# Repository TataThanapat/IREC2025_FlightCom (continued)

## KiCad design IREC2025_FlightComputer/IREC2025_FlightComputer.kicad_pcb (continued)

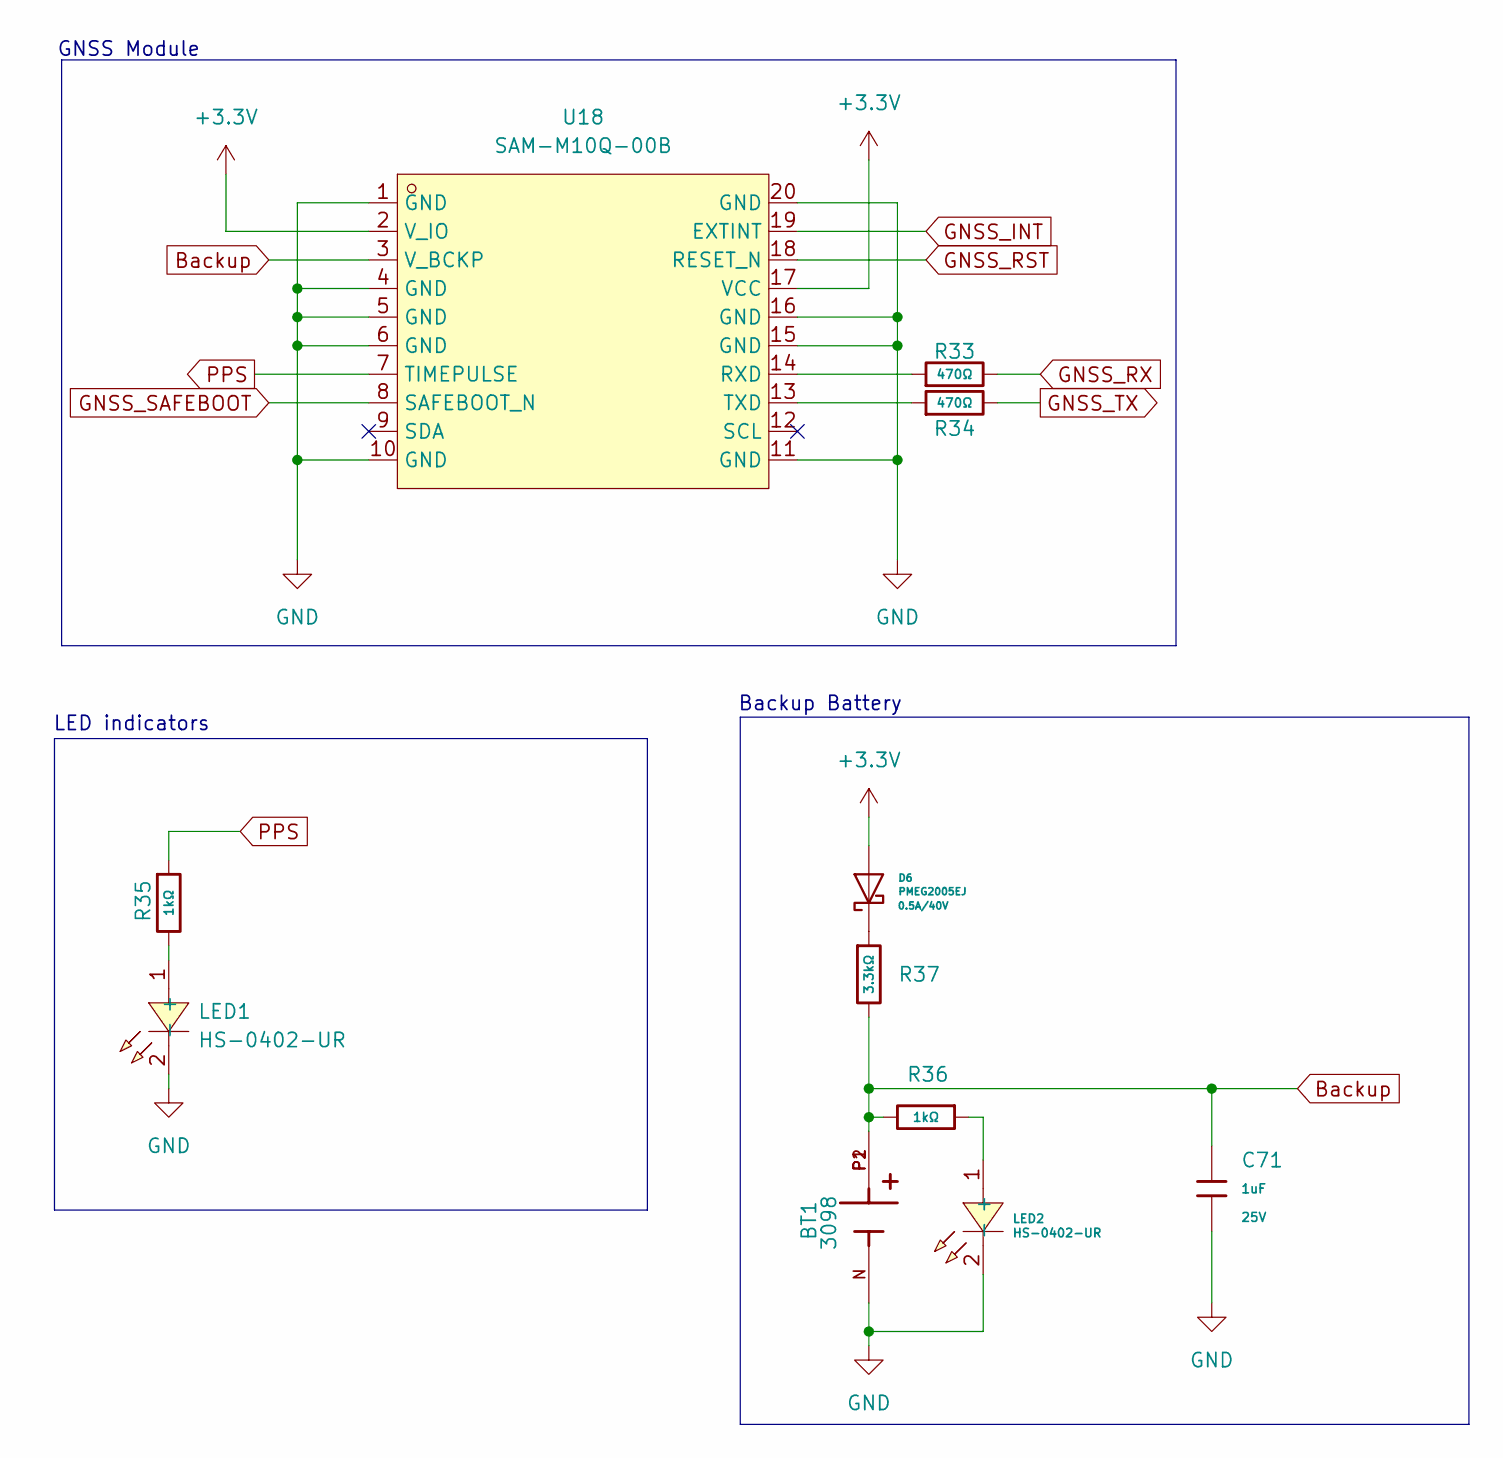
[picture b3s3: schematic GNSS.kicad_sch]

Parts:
BT1: 3098; BAT_3098; PARTREV K
C71: 1uF; C_0402; Voltage Rated 25V; Tolerance ±10%; Part CL05A105KA5NQNC; LCSC C52923
D6: PMEG2005EJ; D_SOD-323F; Ratings 0.5A/40V
LED1, LED2: HS-0402-UR; LED0402-R-RD; LCSC Part C1322304
R33, R34: 470Ω; R_0402; Overload Voltage (Max) 50V; Tolerance ±1%; Part 0402WGF4700TCE; LCSC C25117
R35, R36: 1kΩ; R_0402; Overload Voltage (Max) 50V; Tolerance ±1%; Part 0402WGF1001TCE; LCSC C11702
R37: 3.3kΩ; R_0402; Overload Voltage (Max) 50V; Tolerance ±1%; Part 0402WGF3301TCE; LCSC C25890
U18: SAM-M10Q-00B; LCC-20_L15.5-W15.5-P1.90_SAM-M10Q-00B; LCSC Part C5443880

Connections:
+3.3V: D6.2 (A), U18.2 (V_IO), U18.17 (VCC); also elsewhere on the board
Backup: BT1.P1, BT1.P2, C71.1, R36.2, R37.2, U18.3 (V_BCKP)
GNSS_INT: U18.19 (EXTINT); also elsewhere on the board
GNSS_RST: U18.18 (RESET_N); also elsewhere on the board
GNSS_RX: R33.2; also elsewhere on the board
GNSS_SAFEBOOT: U18.8 (SAFEBOOT_N); also elsewhere on the board
GNSS_TX: R34.2; also elsewhere on the board
unnamed: D6.1 (K), R37.1
unnamed: LED1.1 (+), R35.2
unnamed: LED2.1 (+), R36.1
unnamed: R33.1, U18.14 (RXD)
unnamed: R34.1, U18.13 (TXD)
PPS: R35.1, U18.7 (TIMEPULSE)
VBAT-: BT1.N, C71.2, LED1.2 (-), LED2.2 (-), U18.1 (GND), U18.4 (GND), U18.5 (GND), U18.6 (GND), U18.10 (GND), U18.11 (GND), U18.15 (GND), U18.16 (GND), U18.20 (GND); also elsewhere on the board

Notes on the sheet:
GNSS Module
LED indicators
Backup Battery

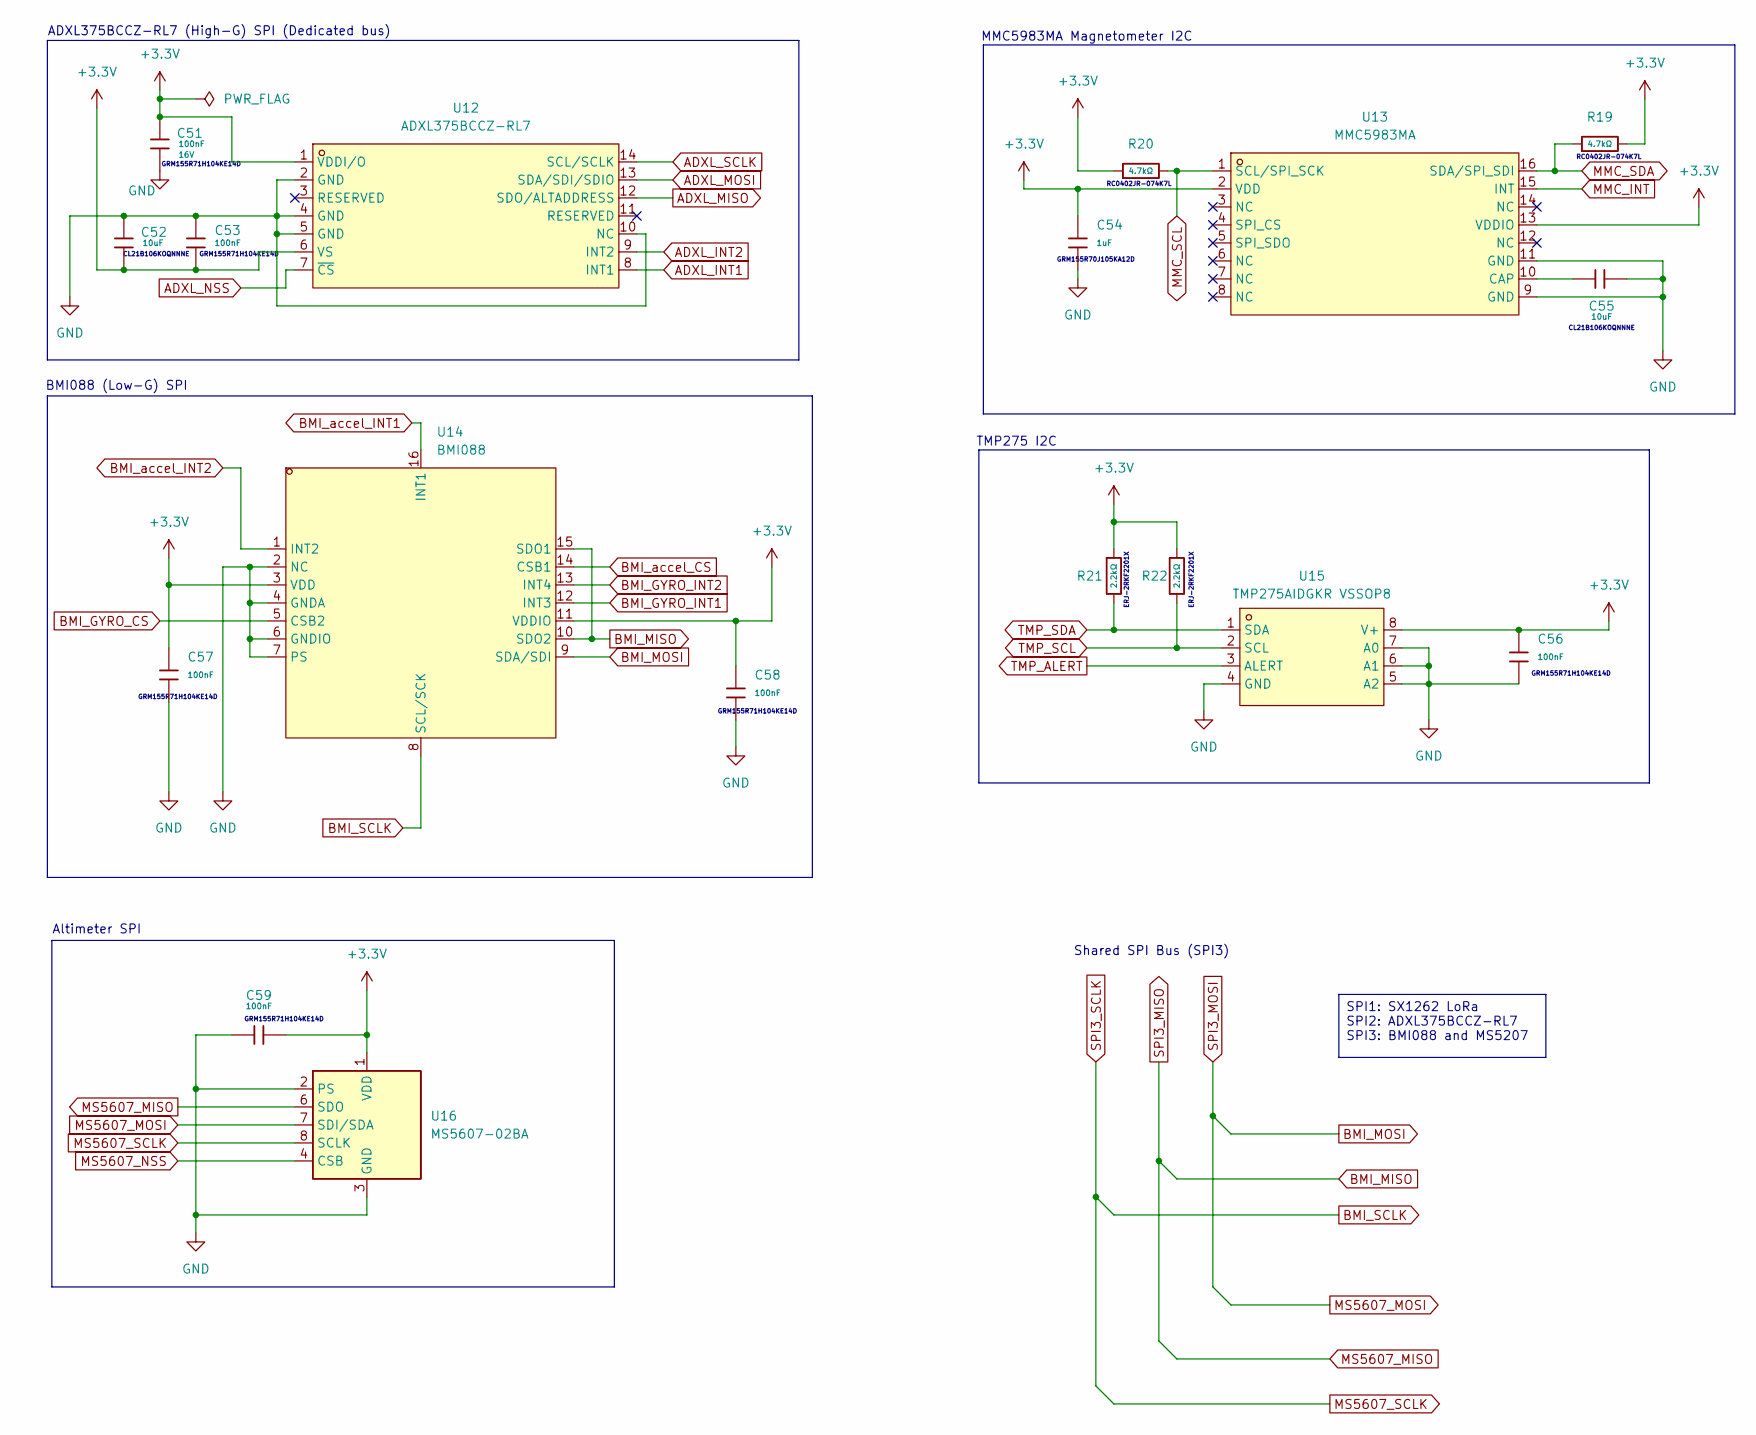
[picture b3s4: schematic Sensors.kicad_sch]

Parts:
C51, C53, C56, C57, C58, C59: 100nF; C_0402; Voltage Rated 16V; Tolerance ±10%; Part CL05B104KO5NNNC; LCSC C1525
C52, C55: 10uF; C_0402; Voltage Rated 6.3V; Tolerance ±20%; Part CL05A106MQ5NUNC; LCSC C15525
C54: 1uF; C_0402; Voltage Rated 25V; Tolerance ±10%; Part CL05A105KA5NQNC; LCSC C52923
R19, R20: 4.7kΩ; R_0402; Overload Voltage (Max) 50V; Tolerance ±1%; Part 0402WGF4701TCE; LCSC C25900
R21, R22: 2.2kΩ; R_0402; Overload Voltage (Max) 50V; Tolerance ±1%; Part 0402WGF2201TCE; LCSC C25879
U12: ADXL375BCCZ-RL7; LGA-14_L5.0-W3.0-P0.80-BL; LCSC Part C481898
U13: MMC5983MA; LGA-16_L3.0-W3.0-P0.50-BL_SQ; LCSC Part C404329
U14: BMI088; LGA-16_L4.5-W3.0-P0.50-BL; LCSC Part C194919
U15: TMP275AIDGKR VSSOP8; VSSOP-8_L3.0-W3.0-P0.65-LS5.0-BL; LCSC Part C87815
U16: MS5607-02BA; LGA-8_3x5mm_P1.25mm

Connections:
+3.3V: C51.1, C52.2, C53.2, C54.1, C56.1, C57.1, C58.1, C59.2, R19.2, R20.1, R21.1, R22.1, U12.1 (VDDI/O), U12.6 (VS), U13.2 (VDD), U13.13 (VDDIO), U14.3 (VDD), U14.11 (VDDIO), U15.8 (V+), U16.1 (VDD); also elsewhere on the board
ADXL_INT1: U12.8 (INT1); also elsewhere on the board
ADXL_INT2: U12.9 (INT2); also elsewhere on the board
ADXL_MISO: U12.12 (SDO/ALTADDRESS); also elsewhere on the board
ADXL_MOSI: U12.13 (SDA/SDI/SDIO); also elsewhere on the board
ADXL_NSS: U12.7 (~CS); also elsewhere on the board
ADXL_SCLK: U12.14 (SCL/SCLK); also elsewhere on the board
BMI_GYRO_CS: U14.5 (CSB2); also elsewhere on the board
BMI_GYRO_INT1: U14.12 (INT3); also elsewhere on the board
BMI_GYRO_INT2: U14.13 (INT4); also elsewhere on the board
BMI_accel_CS: U14.14 (CSB1); also elsewhere on the board
BMI_accel_INT1: U14.16 (INT1); also elsewhere on the board
BMI_accel_INT2: U14.1 (INT2); also elsewhere on the board
MMC_INT: U13.15 (INT); also elsewhere on the board
MMC_SCL: R20.2, U13.1 (SCL/SPI_SCK); also elsewhere on the board
MMC_SDA: R19.1, U13.16 (SDA/SPI_SDI); also elsewhere on the board
MS5607_NSS: U16.4 (CSB), U16.5 (CSB); also elsewhere on the board
unnamed: C55.1, U13.10 (CAP)
TMP_ALERT: U15.3 (ALERT); also elsewhere on the board
TMP_SCL: R22.2, U15.2 (SCL); also elsewhere on the board
TMP_SDA: R21.2, U15.1 (SDA); also elsewhere on the board
VBAT-: C51.2, C52.1, C53.1, C54.2, C55.2, C56.2, C57.2, C58.2, C59.1, U12.2 (GND), U12.4 (GND), U12.5 (GND), U12.10 (NC), U13.9 (GND), U13.11 (GND), U14.2 (NC), U14.4 (GNDA), U14.6 (GNDIO), U14.7 (PS), U15.4 (GND), U15.5 (A2), U15.6 (A1), U15.7 (A0), U16.2 (PS), U16.3 (GND); also elsewhere on the board

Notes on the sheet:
Shared SPI Bus (SPI3)
ERJ-2RKF2201X
CL21B106KOQNNNE
GRM155R71H104KE14D
RC0402JR-074K7L
GRM155R70J105KA12D
TMP275 I2C
BMI088 (Low-G) SPI
MMC5983MA Magnetometer I2C
ADXL375BCCZ-RL7 (High-G) SPI (Dedicated bus)
Altimeter SPI
SPI1: SX1262 LoRa SPI2: ADXL375BCCZ-RL7 SPI3: BMI088 and MS5207

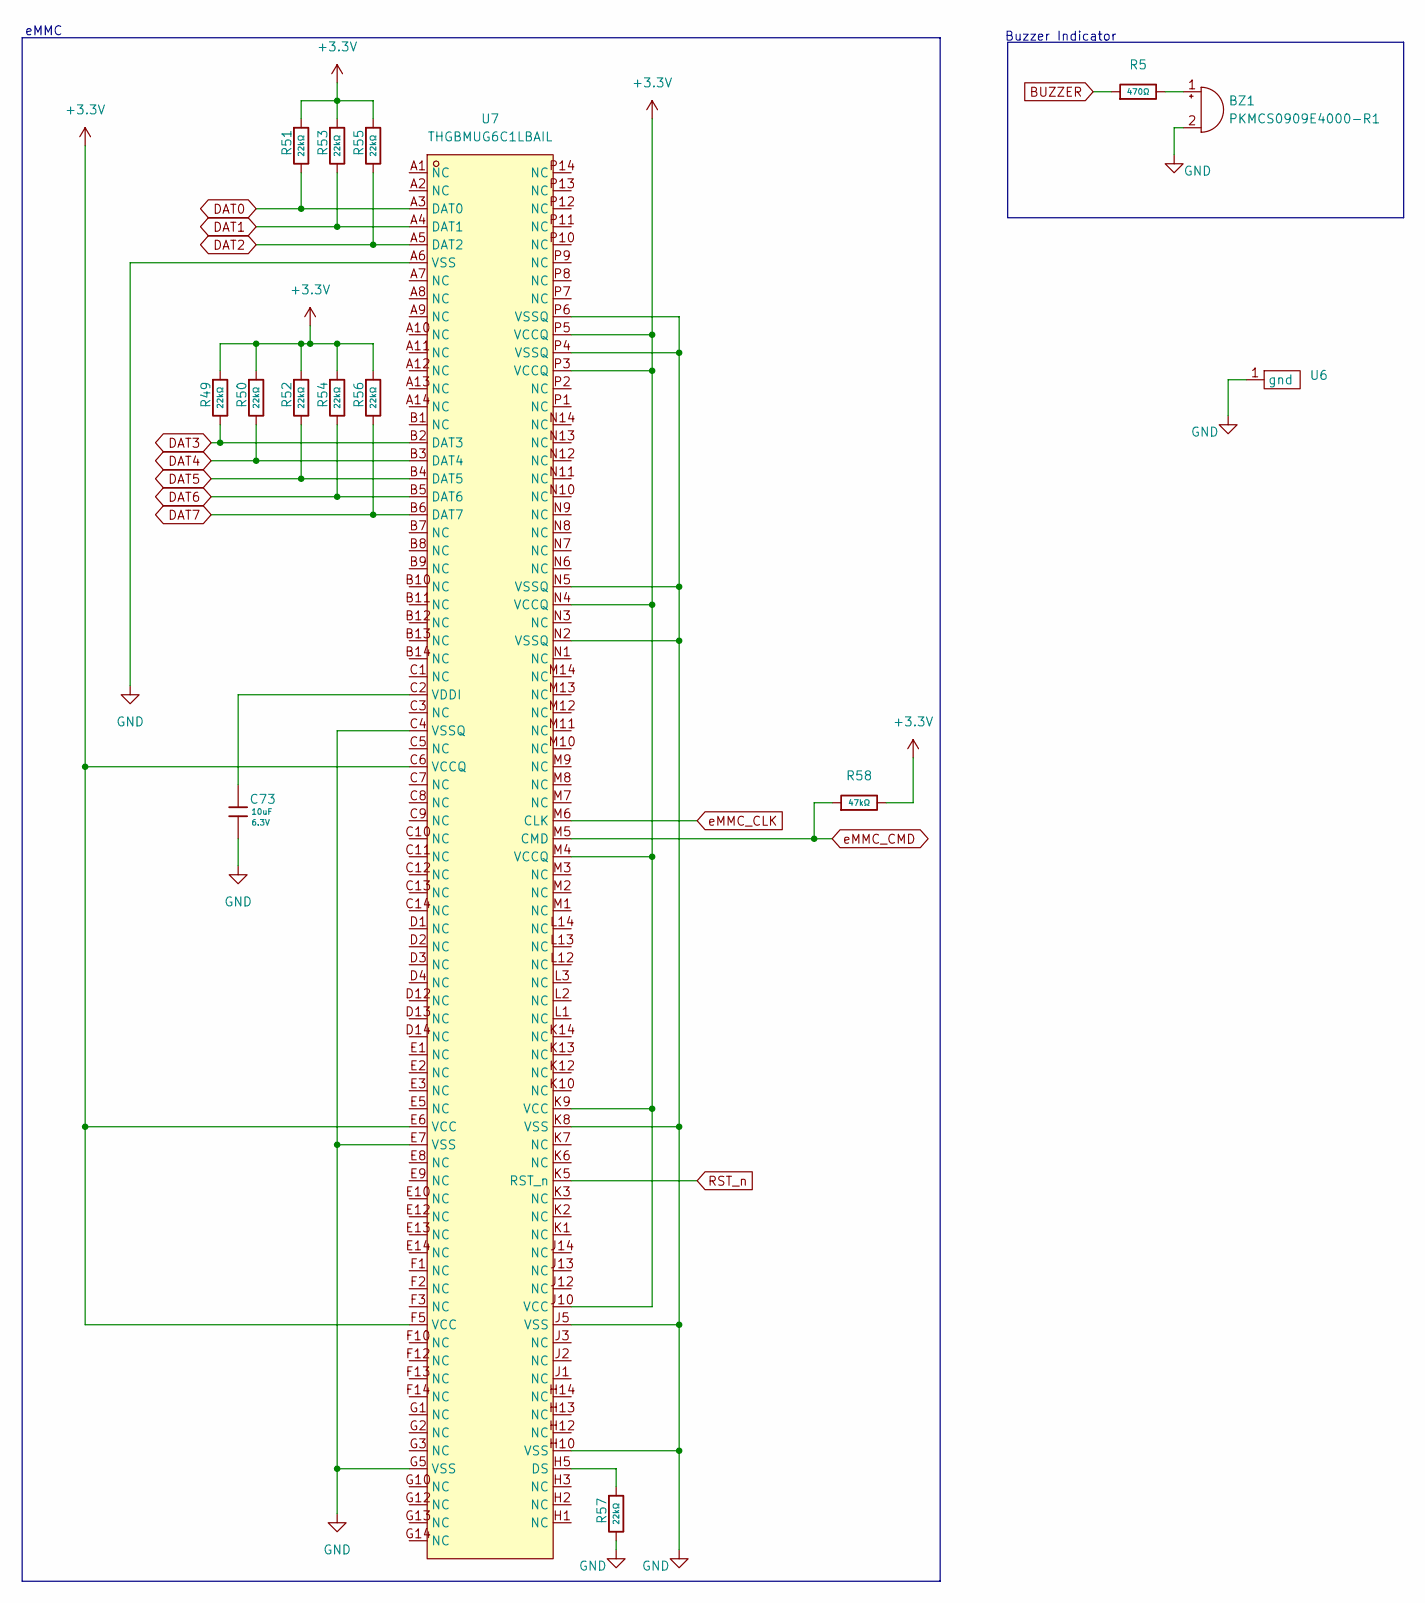
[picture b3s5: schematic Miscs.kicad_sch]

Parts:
BZ1: PKMCS0909E4000-R1; PUIAudio_SMT_0825_S_4_R
C73: 10uF; C_0402; Voltage Rated 6.3V; Tolerance ±20%; Part CL05A106MQ5NUNC; LCSC C15525
R5: 470Ω; R_0402; Overload Voltage (Max) 50V; Tolerance ±1%; Part 0402WGF4700TCE; LCSC C25117
R49, R50, R51, R52, R53, R54, R55, R56, R57: 22kΩ; R_0402; Overload Voltage (Max) 50V; Tolerance ±1%; Part 0402WGF2202TCE; LCSC C25768
R58: 47kΩ; R_0402; Overload Voltage (Max) 50V; Tolerance ±1%; Part 0402WGF4702TCE; LCSC C25792
U6: MS233-20
U7: THGBMUG6C1LBAIL; BGA-153_L13.0-W11.5-P0.50-TL_KLM8G1GEME-B041; LCSC Part C7509349

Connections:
+3.3V: R49.1, R50.1, R51.1, R52.1, R53.1, R54.1, R55.1, R56.1, R58.2, U7.C6 (VCCQ), U7.E6 (VCC), U7.F5 (VCC), U7.J10 (VCC), U7.K9 (VCC), U7.M4 (VCCQ), U7.N4 (VCCQ), U7.P3 (VCCQ), U7.P5 (VCCQ); also elsewhere on the board
BUZZER: R5.1; also elsewhere on the board
DAT0: R51.2, U7.A3 (DAT0); also elsewhere on the board
DAT1: R53.2, U7.A4 (DAT1); also elsewhere on the board
DAT2: R55.2, U7.A5 (DAT2); also elsewhere on the board
DAT3: R49.2, U7.B2 (DAT3); also elsewhere on the board
DAT4: R50.2, U7.B3 (DAT4); also elsewhere on the board
DAT5: R52.2, U7.B4 (DAT5); also elsewhere on the board
DAT6: R54.2, U7.B5 (DAT6); also elsewhere on the board
DAT7: R56.2, U7.B6 (DAT7); also elsewhere on the board
unnamed: BZ1.1 (+), R5.2
unnamed: R57.1, U7.H5 (DS)
unnamed: C73.1, U7.C2 (VDDI)
RST_n: U7.K5 (RST_n); also elsewhere on the board
VBAT-: BZ1.2 (-), C73.2, R57.2, U6.1 (gnd), U7.A6 (VSS), U7.C4 (VSSQ), U7.E7 (VSS), U7.G5 (VSS), U7.H10 (VSS), U7.J5 (VSS), U7.K8 (VSS), U7.N2 (VSSQ), U7.N5 (VSSQ), U7.P4 (VSSQ), U7.P6 (VSSQ); also elsewhere on the board
eMMC_CLK: U7.M6 (CLK); also elsewhere on the board
eMMC_CMD: R58.1, U7.M5 (CMD); also elsewhere on the board

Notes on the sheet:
Buzzer Indicator
eMMC

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
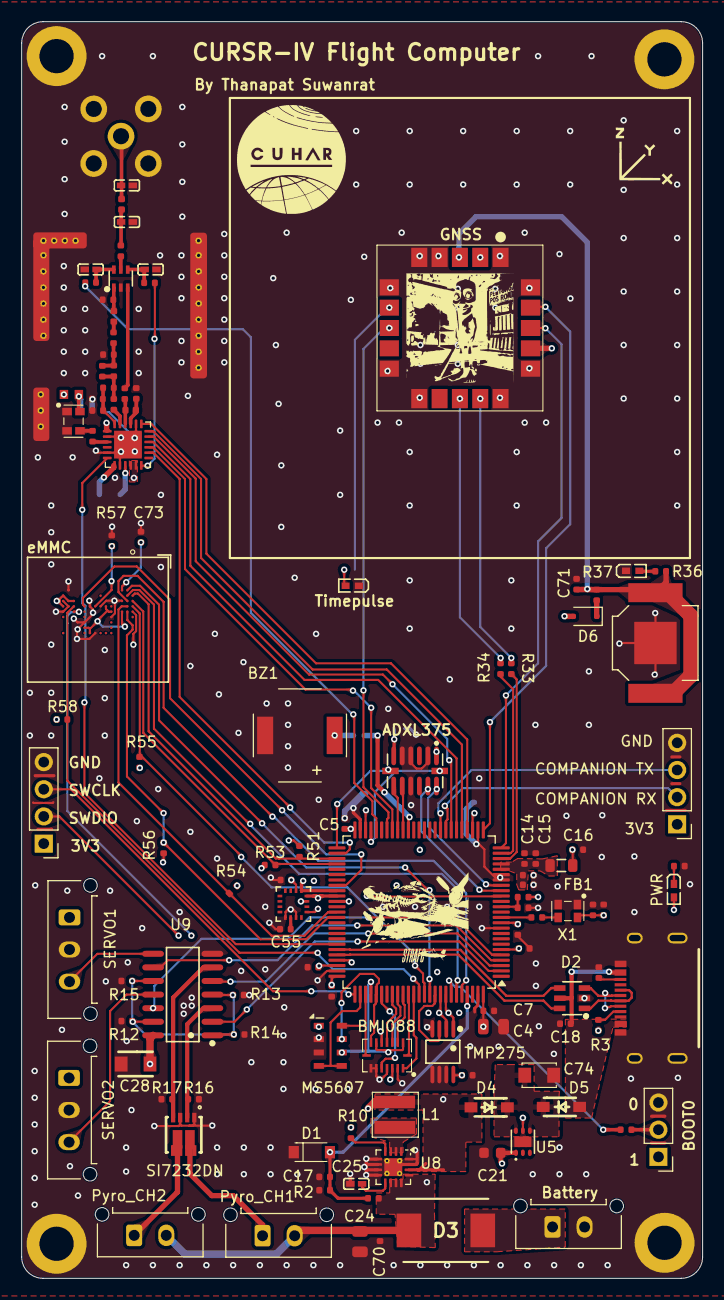
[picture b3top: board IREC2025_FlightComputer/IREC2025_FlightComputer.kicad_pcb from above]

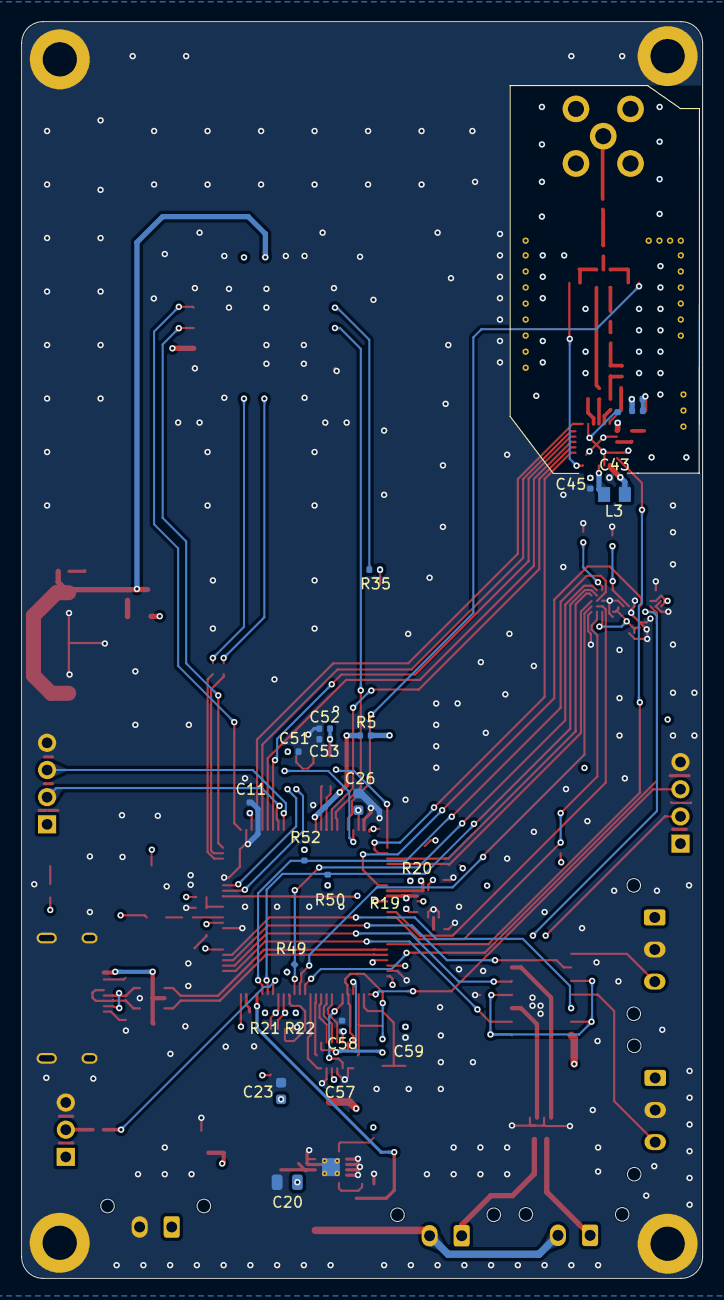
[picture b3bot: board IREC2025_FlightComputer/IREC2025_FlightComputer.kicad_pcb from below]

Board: 4 copper layers, 63.6 x 117.5 mm, 147 parts (25 on the bottom side), 118 nets.

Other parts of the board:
LOGO: LOGO; CUHARLOGOMOD

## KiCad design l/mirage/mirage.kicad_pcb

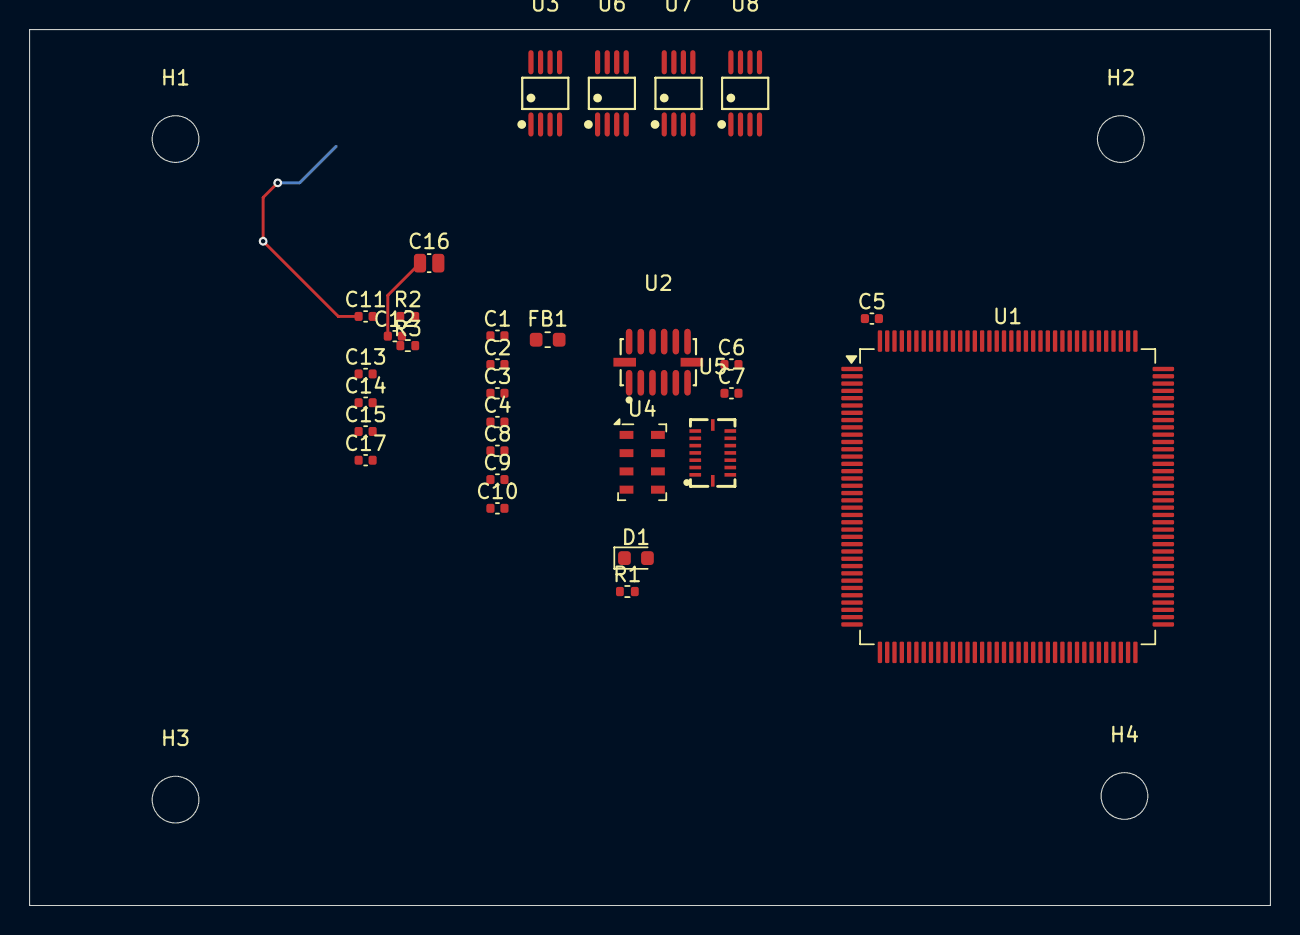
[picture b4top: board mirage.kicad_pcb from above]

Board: 2 copper layers, 85.0 x 60.0 mm, 34 parts (0 on the bottom side), 13 nets.

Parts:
C1, C2, C3, C4, C5, C6, C7, C11, C12, C14, C15, C17: 100nF; C_0402_1005Metric
C8: 100n; C_0402_1005Metric
C9, C10: 10n; C_0402_1005Metric
C13: 10uF; C_0402_1005Metric
C16: 100nF; C_0504_1310Metric_Pad0.83x1.28mm_HandSolder
D1: LED Yellow; LED_0603_1608Metric
FB1: 120R; L_0603_1608Metric
H1, H2, H3, H4: MountingHole; MountingHole_3.2mm_M3
R1: 1K0R; R_0402_1005Metric
R2, R3: 5k; R_0402_1005Metric
U1: STM32H573ZITx; LQFP-144_20x20mm_P0.5mm
U2: ADXL375BCCZ-RL7; LGA-14_L5.0-W3.0-P0.80-BL
U3, U6, U7, U8: TMP275AIDGKR VSSOP8; VSSOP-8_L3.0-W3.0-P0.65-LS5.0-BL
U4: MS5607-02BA; LGA-8_3x5mm_P1.25mm
U5: BMI088; LGA-16_L4.5-W3.0-P0.50-BL

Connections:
+3.3V: C1.1, C2.1, C3.1, C4.1, C5.2, C6.1, C7.1, C10.1, C14.1, C15.1, C16.2, C17.2, FB1.2, R2.1, R3.1, U1.17 (VDD), U1.30 (VDD), U1.39 (VDD), U1.52 (VDD), U1.62 (VDD), U1.72 (VDD), U1.84 (VDD), U1.95 (VDD), U1.108 (VDD), U1.131 (VDD), U1.144 (VDD), U3.8 (V+), U4.1 (VDD), U5.3 (VDD), U5.11 (VDDIO), U6.6 (A1), U6.8 (V+), U7.7 (A0), U7.8 (V+), U8.6 (A1), U8.7 (A0), U8.8 (V+)
+3.3VA: C8.1, C9.1, FB1.1, U1.33 (VDDA)
/Sensors/TMP275_SCL: R3.2, U3.2 (SCL), U6.2 (SCL), U7.2 (SCL), U8.2 (SCL)
/Sensors/TMP275_SDA: R2.2, U3.1 (SDA), U6.1 (SDA), U7.1 (SDA), U8.1 (SDA)
BMI088_MISO: U5.10 (SDO2), U5.15 (SDO1)
GND: C1.2, C2.2, C3.2, C4.2, C5.1, C6.2, C7.2, C8.2, C9.2, C10.2, C11.2, C12.1, C13.1, C14.2, C15.2, C16.1, C17.1, R1.2, U1.16 (VSS), U1.31 (VSSA), U1.38 (VSS), U1.51 (VSS), U1.61 (VSS), U1.71 (VSS), U1.83 (VSS), U1.94 (VSS), U1.107 (VSS), U1.120 (VSS), U1.130 (VSS), U1.143 (VSS), U2.4 (GND), U3.4 (GND), U3.5 (A2), U3.6 (A1), U3.7 (A0), U4.2 (PS), U4.3 (GND), U5.2 (NC), U5.4 (GNDA), U5.6 (GNDIO), U5.7 (PS), U6.4 (GND), U6.5 (A2), U6.7 (A0), U7.4 (GND), U7.5 (A2), U7.6 (A1), U8.4 (GND), U8.5 (A2)
MS5607_NSS: U4.4 (CSB), U4.5 (CSB)
MS5607_SCLK: U2.14 (SCL/SCLK), U4.8 (SCLK)
unnamed: D1.1 (K), R1.1
unnamed: U2.2 (GND), U2.5 (GND)
unnamed: C11.1, U2.1 (VDDI/O)
unnamed: C12.2, C13.2, U2.6 (VS)
unnamed: U5.12 (INT3), U5.16 (INT1)

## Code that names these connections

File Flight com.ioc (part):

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Mcu.Name=STM32U575VGTx
Mcu.Package=LQFP100
Mcu.UserName=STM32U575VGTx
PA0.GPIOParameters=GPIO_Label
PA0.GPIO_Label=GNSS_TX
PA0.Mode=Asynchronous
PA0.Signal=UART4_TX
PA1.GPIOParameters=GPIO_Label
PA1.GPIO_Label=GNSS_RX
PA1.Mode=Asynchronous
PA1.Signal=UART4_RX
PA10.GPIOParameters=GPIO_Label
PA10.GPIO_Label=LoRa_INT
PA10.Signal=GPXTI10
PA11.Mode=Device_Only
PA11.Signal=USB_OTG_FS_DM
PA12.Mode=Device_Only
PA12.Signal=USB_OTG_FS_DP
PA13\ (JTMS/SWDIO).Mode=Serial_Wire
PA13\ (JTMS/SWDIO).Signal=DEBUG_JTMS-SWDIO
PA14\ (JTCK/SWCLK).Mode=Serial_Wire
PA14\ (JTCK/SWCLK).Signal=DEBUG_JTCK-SWCLK
PA15\ (JTDI).GPIOParameters=GPIO_Label
PA15\ (JTDI).GPIO_Label=MS5607_NSS
PA15\ (JTDI).Mode=NSS_Signal_Hard_Output
PA15\ (JTDI).Signal=SPI3_NSS
PA2.GPIOParameters=GPIO_Label
PA2.GPIO_Label=GNSS_RST
PA2.Signal=GPIO_Output
PA4.Mode=NSS_Signal_Hard_Output
PA4.Signal=SPI1_NSS
PA5.Mode=Full_Duplex_Master
PA5.Signal=SPI1_SCK
PA6.Mode=Full_Duplex_Master
PA6.Signal=SPI1_MISO
PA7.Mode=Full_Duplex_Master
PA7.Signal=SPI1_MOSI
PB10.Mode=Full_Duplex_Master
PB10.Signal=SPI2_SCK
PB12.Mode=NSS_Signal_Hard_Output
PB12.Signal=SPI2_NSS
PB13.GPIOParameters=GPIO_Label
PB13.GPIO_Label=LORA_BUSY
PB13.Signal=GPIO_Input
PB14.Mode=mmc_8_bits_Wide_bus
PB14.Signal=SDMMC2_D0
PB15.Mode=mmc_8_bits_Wide_bus
PB15.Signal=SDMMC2_D1
PB3\ (JTDO/TRACESWO).Mode=mmc_8_bits_Wide_bus
PB3\ (JTDO/TRACESWO).Signal=SDMMC2_D2
PB4\ (NJTRST).Mode=mmc_8_bits_Wide_bus
PB4\ (NJTRST).Signal=SDMMC2_D3
PB5.GPIOParameters=GPIO_Label
PB5.GPIO_Label=TMP_ALERT
PB5.Signal=GPIO_Input
PB6.Mode=I2C
PB6.Signal=I2C1_SCL
PB7.Mode=I2C
PB7.Signal=I2C1_SDA
PB8.Mode=mmc_8_bits_Wide_bus
PB8.Signal=SDMMC2_D4
PB9.Mode=mmc_8_bits_Wide_bus
PB9.Signal=SDMMC2_D5
PC1.Mode=mmc_8_bits_Wide_bus
PC1.Signal=SDMMC2_CK
PC10.Mode=Full_Duplex_Master
PC10.Signal=SPI3_SCK
PC11.Mode=Full_Duplex_Master
PC11.Signal=SPI3_MISO
PC12.Mode=Full_Duplex_Master
PC12.Signal=SPI3_MOSI
PC2.Mode=Full_Duplex_Master
PC2.Signal=SPI2_MISO
PC3.Mode=Full_Duplex_Master
PC3.Signal=SPI2_MOSI
PC4.GPIOParameters=GPIO_Label
PC4.GPIO_Label=COMPANION_TX
PC4.Mode=Asynchronous
PC4.Signal=USART3_TX
PC5.GPIOParameters=GPIO_Label
PC5.GPIO_Label=COMPANION_RX
PC5.Mode=Asynchronous
PC5.Signal=USART3_RX
PC6.Mode=mmc_8_bits_Wide_bus
PC6.Signal=SDMMC2_D6
PC7.Mode=mmc_8_bits_Wide_bus
PC7.Signal=SDMMC2_D7
PD0.GPIOParameters=GPIO_Label
PD0.GPIO_Label=GYRO_CS
PD0.Signal=GPIO_Output
PD1.Signal=GPIO_Output
PD12.Mode=I2C
PD12.Signal=I2C4_SCL
PD13.Mode=I2C
PD13.Signal=I2C4_SDA
PD2.GPIOParameters=GPIO_Label
PD2.GPIO_Label=ACCEL_INT
PD2.Signal=GPXTI2
PD3.GPIOParameters=GPIO_Label
PD3.GPIO_Label=GYRO_INT
PD3.Signal=GPXTI3
PD5.GPIOParameters=GPIO_Label
PD5.GPIO_Label=ACCEL_CS
PD5.Signal=GPIO_Output
PD7.Mode=mmc_8_bits_Wide_bus
PD7.Signal=SDMMC2_CMD
PE11.GPIOParameters=GPIO_Label
PE11.GPIO_Label=ADXL_INT1
PE11.Signal=GPXTI11
PE12.GPIOParameters=GPIO_Label
PE12.GPIO_Label=LORA_RST
PE12.Signal=GPIO_Output
PE13.GPIOParameters=GPIO_Label
PE13.GPIO_Label=GNSS_SAFEBOOT
PE13.Signal=GPIO_Output
PE15.GPIOParameters=GPIO_Label
PE15.GPIO_Label=ANT_SW
PE15.Signal=GPIO_Output
PE3.GPIOParameters=GPIO_Label
PE3.GPIO_Label=PWM_A
PE3.Signal=S_TIM3_CH1
PE4.GPIOParameters=GPIO_Label
PE4.GPIO_Label=PWM_B
PE4.Signal=S_TIM3_CH2
PE5.GPIOParameters=GPIO_Label
PE5.GPIO_Label=PWM_C
PE5.Signal=S_TIM3_CH3
PE6.GPIOParameters=GPIO_Label
PE6.GPIO_Label=PWM_D
PE6.Signal=S_TIM3_CH4
PE9.GPIOParameters=GPIO_Label
PE9.GPIO_Label=Buzzer
PE9.Signal=S_TIM1_CH1
PH0-OSC_IN\ (PH0).Mode=HSE-External-Oscillator
PH0-OSC_IN\ (PH0).Signal=RCC_OSC_IN
PH1-OSC_OUT\ (PH1).Mode=HSE-External-Oscillator
PH1-OSC_OUT\ (PH1).Signal=RCC_OSC_OUT
PH3-BOOT0.GPIOParameters=GPIO_Label
PH3-BOOT0.GPIO_Label=BOOT0
PH3-BOOT0.Signal=GPIO_Input
RCC.HSE_VALUE=16000000
board=custom

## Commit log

2025-03-19 First
2025-03-19 Schematics
2025-03-21 update
    21/3/2025
2025-03-22 Updated 22/3/2025
2025-03-23 Updated schematic + initiate layout
2025-03-24 update idk
    25/3/2025
    starting to take shape (i guess)
2025-04-12 checkpoint
    before the great layout change
2025-04-14 Layout change
    Layout changes (Particularly GNSS and LoRa)
2025-04-15 Added via stitching
2025-04-15 small fixes
2025-04-17 Minor changes
2025-04-18 Added silkscreen + Layout Minorchange
2025-04-19 Schematics minor fixes
2025-04-20 USB Differentials matched to 90R
2025-04-20 forgor mmc int :( added
2025-04-25 2 designs
2025-04-30 changed most resistors to 0603
2025-05-02 Chore: Remove useless folders
2025-05-02 Chore: push new design
2025-05-03 update layout
2025-05-03 tung tung tung
2025-05-03 Add current limit to servo
2025-05-03 Special version
2025-05-04 Chore: Add Digikey Part to symbols
2025-05-04 v2 manufactured ver.
2025-05-04 Final manu v2
2025-05-16 Complete Redesign
2025-05-17 updated SD
2025-05-18 fkdjgfg
2025-05-18 Feat: Minor improvement
2025-05-18 Feat: Replace old LDO with better LDO
2025-05-18 Feat: Finish superior LDO route
2025-05-18 Feat: add silkscreen
2025-05-19 Added silkscreen + Changed gps vbackup
2025-05-19 adjustments
2025-05-20 Ordered version
2025-05-31 fixes
    Fixed mmc, power
    Added external 5V Supply
    Added external reset button
2025-05-31 lmao
